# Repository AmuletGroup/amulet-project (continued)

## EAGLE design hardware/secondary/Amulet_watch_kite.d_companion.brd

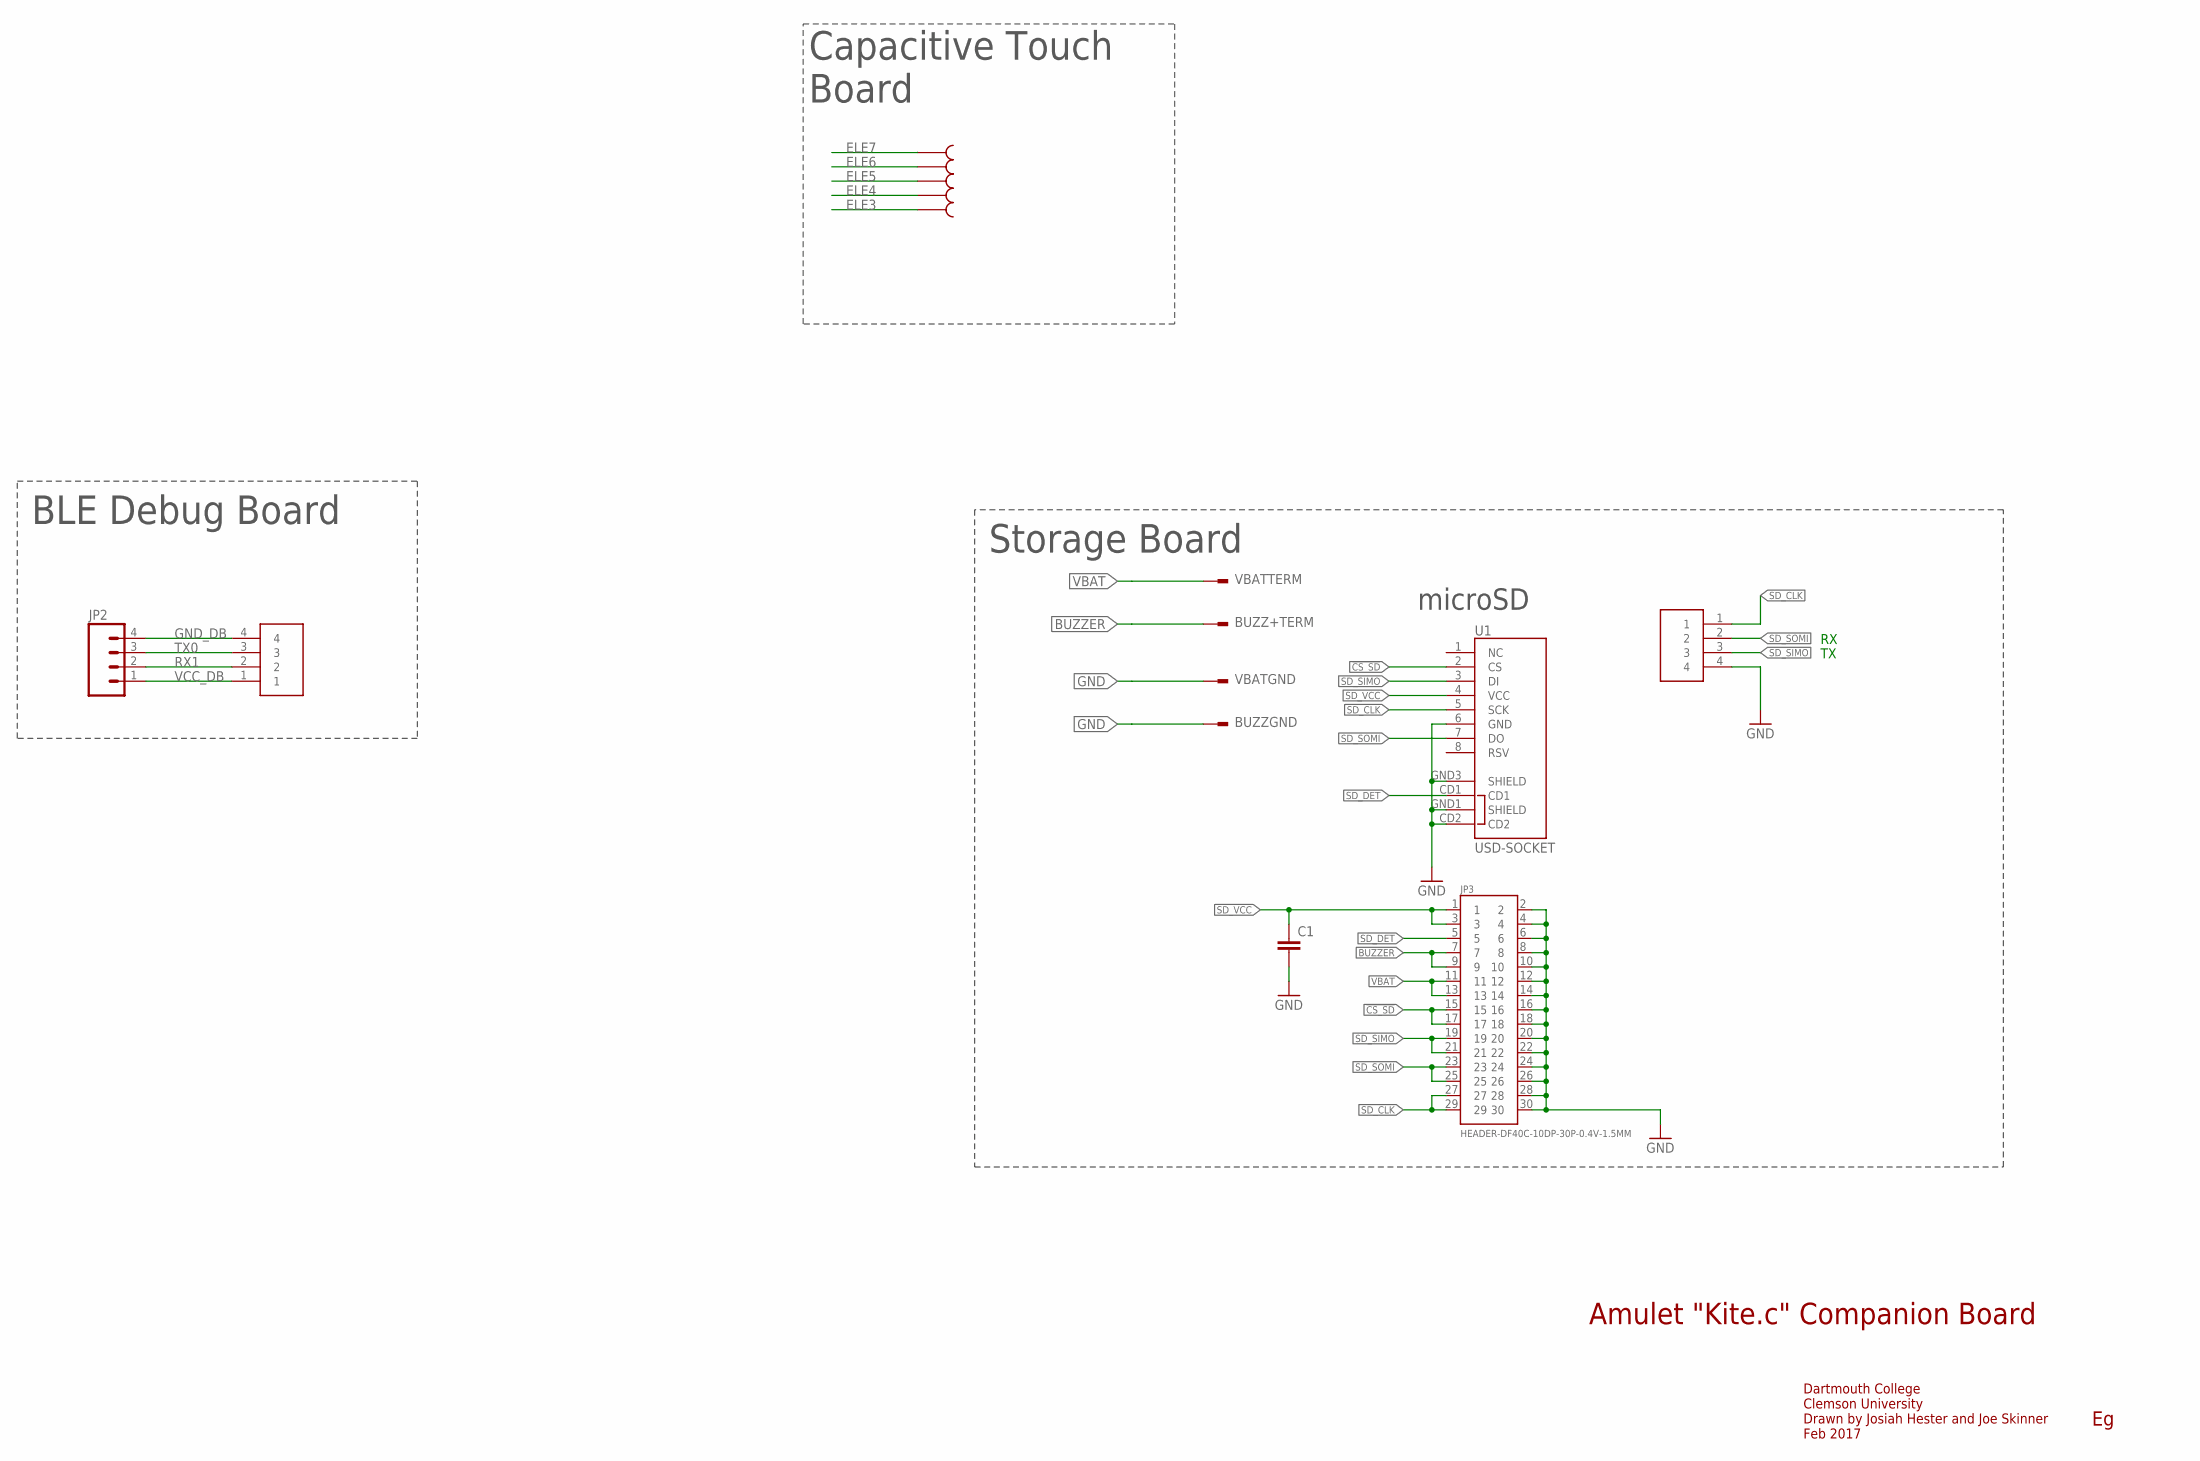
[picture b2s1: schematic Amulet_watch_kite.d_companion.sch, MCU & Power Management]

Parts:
BUZZ+TERM: KITE.C.TERMINAL; BATTERY_TERMINAL
BUZZGND: KITE.C.TERMINAL; BATTERY_TERMINAL
C1: CAP0805; 0805
JP2: M04LOCK; 1X04_LOCK
JP3: HEADER-DF40C-10DP-30P-0.4V-1.5MM; HEADER-DF40-30; DIGIKEY H11622CT-ND
U1: USD-SOCKET; MICROSD_1:1
U$1, U$2, U$3, U$4, U$5: CTPAD
U$11, U$12: 1.27MM-MILLMAX; 1X03-1.27MM
VBATGND: KITE.C.TERMINAL; BATTERY_TERMINAL
VBATTERM: KITE.C.TERMINAL; BATTERY_TERMINAL

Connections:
!CS_SD: JP3.15, JP3.17, U1.2 (CS)
BUZZER: BUZZ+TERM.P1, JP3.7, JP3.9
ELE3: U$5.P$1
ELE4: U$4.P$1
ELE5: U$3.P$1
ELE6: U$2.P$1
ELE7: U$1.P$1
GND: BUZZGND.P1, C1.2, JP3.2, JP3.4, JP3.6, JP3.8, JP3.10, JP3.12, JP3.14, JP3.16, JP3.18, JP3.20, JP3.22, JP3.24, JP3.26, JP3.28, JP3.30, U1.6 (GND), U1.CD2, U1.GND1 (SHIELD), U1.GND3 (SHIELD), U$11.4, VBATGND.P1
GND_DB: JP2.4, U$12.4
RX1: JP2.2, U$12.2
SD_CLK: JP3.27, JP3.29, U1.5 (SCK), U$11.1
SD_DET: JP3.5, U1.CD1
SD_SIMO: JP3.19, JP3.21, U1.3 (DI), U$11.3
SD_SOMI: JP3.23, JP3.25, U1.7 (DO), U$11.2
SD_VCC: C1.1, JP3.1, JP3.3, U1.4 (VCC)
TX0: JP2.3, U$12.3
VBAT: JP3.11, JP3.13, VBATTERM.P1
VCC_DB: JP2.1, U$12.1

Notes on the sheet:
Amulet "Kite.c" Companion Board
Dartmouth College Clemson University Drawn by Josiah Hester and Joe Skinner Feb 2017
microSD
Capacitive Touch Board
Storage Board
BLE Debug Board

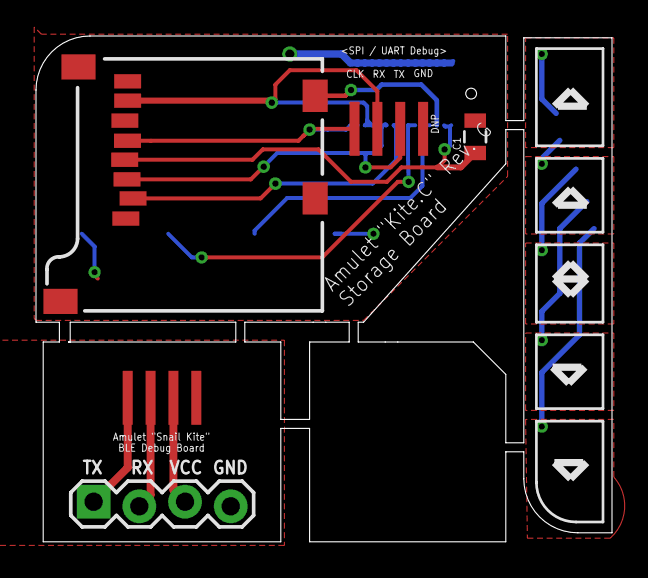
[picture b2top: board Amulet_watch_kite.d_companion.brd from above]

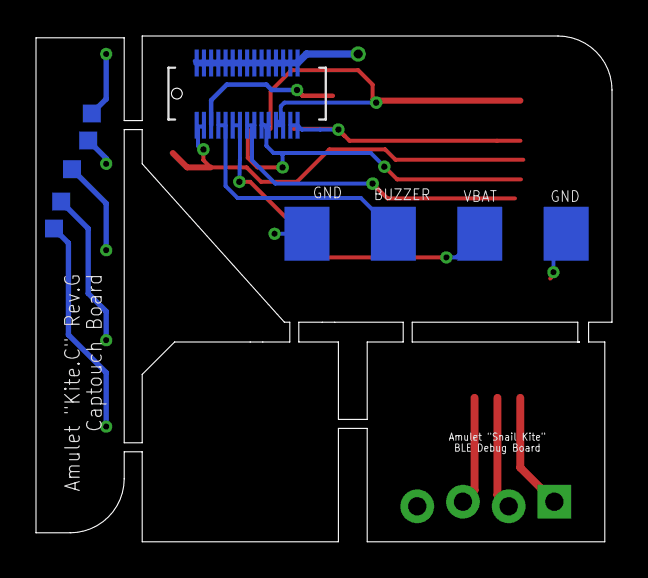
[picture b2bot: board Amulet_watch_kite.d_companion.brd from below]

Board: 2 copper layers, 32.0 x 28.1 mm, 15 parts (10 on the bottom side), 13 nets.

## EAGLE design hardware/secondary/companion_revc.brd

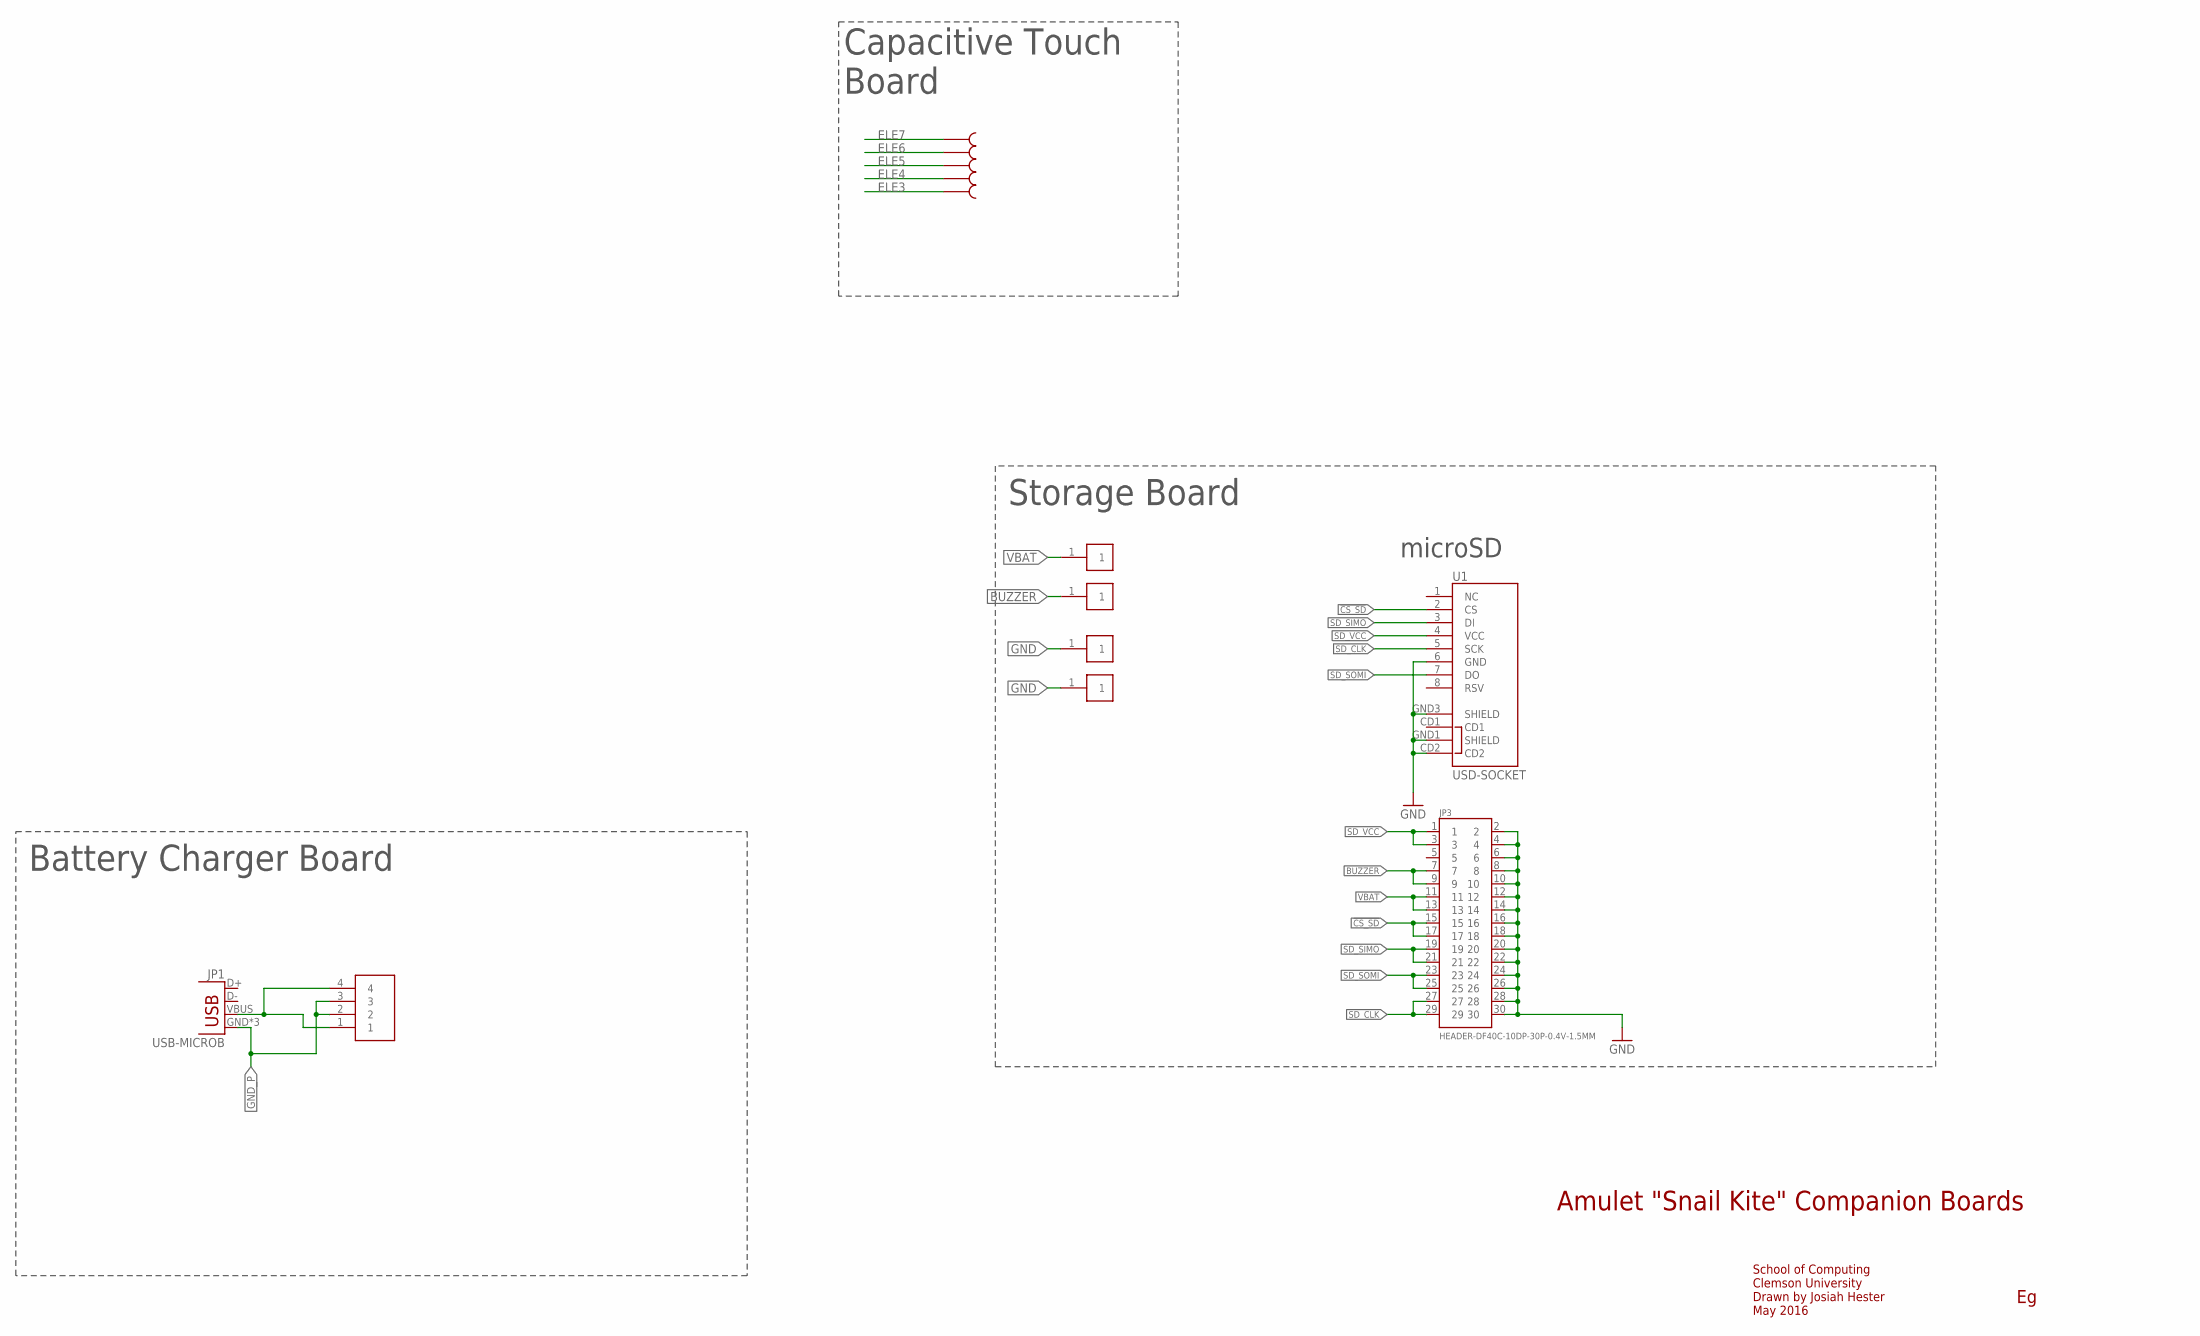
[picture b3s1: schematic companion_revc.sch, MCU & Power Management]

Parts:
JP1: USB-MICROB
JP3: HEADER-DF40C-10DP-30P-0.4V-1.5MM; HEADER-DF40-30
U1: USD-SOCKET; MICROSD_1:1
U$1, U$2, U$3, U$4, U$5: CTPAD
U$6, U$7, U$8, U$9: 1PAD; 5X23MM_PAD
U$10: 1.27MM-MILLMAX; 1X03-1.27MM

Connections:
!CS_SD: JP3.15, JP3.17, U1.2 (CS)
BUZZER: JP3.7, JP3.9, U$7.1
ELE3: U$5.P$1
ELE4: U$4.P$1
ELE5: U$3.P$1
ELE6: U$2.P$1
ELE7: U$1.P$1
GND: JP3.2, JP3.4, JP3.6, JP3.8, JP3.10, JP3.12, JP3.14, JP3.16, JP3.18, JP3.20, JP3.22, JP3.24, JP3.26, JP3.28, JP3.30, U1.6 (GND), U1.CD2, U1.GND1 (SHIELD), U1.GND3 (SHIELD), U$8.1, U$9.1
GND_P: JP1.GND, JP1.MT1 (GND), JP1.MT2 (GND), U$10.2, U$10.3
SD_CLK: JP3.27, JP3.29, U1.5 (SCK)
SD_SIMO: JP3.19, JP3.21, U1.3 (DI)
SD_SOMI: JP3.23, JP3.25, U1.7 (DO)
SD_VCC: JP3.1, JP3.3, U1.4 (VCC)
USB_VIN: JP1.VBUS, U$10.1, U$10.4
VBAT: JP3.11, JP3.13, U$6.1

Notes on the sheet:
Amulet "Snail Kite" Companion Boards
School of Computing Clemson University Drawn by Josiah Hester May 2016
microSD
Capacitive Touch Board
Battery Charger Board
Storage Board

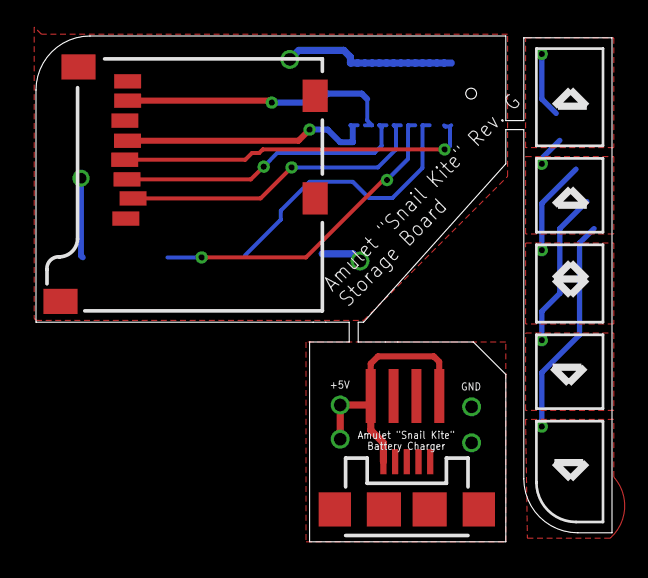
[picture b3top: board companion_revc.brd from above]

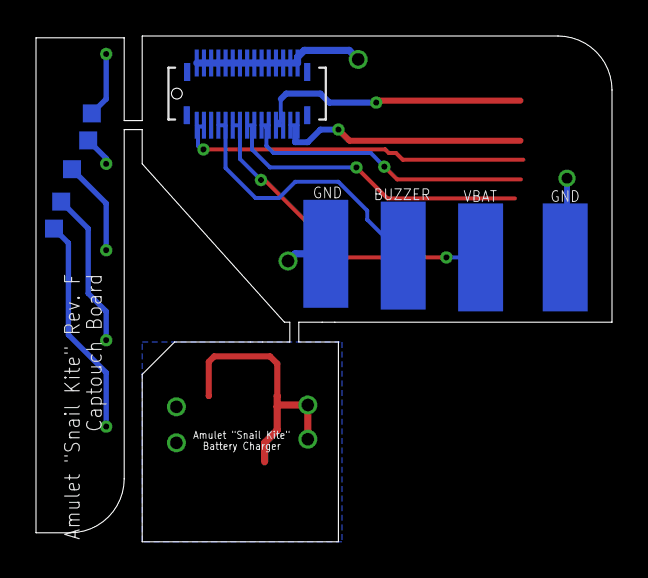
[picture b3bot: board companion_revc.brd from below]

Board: 2 copper layers, 32.0 x 28.1 mm, 13 parts (10 on the bottom side), 10 nets.

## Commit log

2016-08-31 Removed TODO
2016-08-31 Added license text to remaining files, and to CAD EAGLE schematics.
2016-09-08 updated modules
2016-09-08 corrected lib-qpc path
2016-09-21 updated paths for cloning git repo
2016-09-25 Moving lib-qpc back into the native folder
2016-09-26 Misspelled configuration
2016-09-26 Try catch on parsing to skip errors.
2016-10-25 New hardware revision, better connector.
2016-10-25 Update to clock app.
2016-11-07 New case designs.
2016-11-15 updating blink application
2016-11-15 adding readme files for applications
2016-11-15 updating pedometer and uidemo apps
2016-11-15 updated pedometer and uidemo apps
2016-11-15 updated readme files for pedometer and uidemo
2016-11-15 added readme files for ema and heartrate
2016-11-15 updated firmware and software readme files
2016-11-15 updated broken link in software readme
2016-11-15 updated getting started guide
2016-11-15 added image of example qm application
2016-11-15 updated links in example firmware config file and broken link in software readme
2016-11-15 updated ARP view link
2016-11-15 Added submodule commands in case recursive flag does not work
2016-11-15 updated sd card code for the amulet kite hardware version
2016-11-15 added bug tracking note to readme
2016-11-15 removed bugs file
2016-11-15 created issues subsection
2017-05-23 updated the getting started guide. Added picture for programmer hookup
2017-05-23 added programmer hookup picture
2017-05-23 updated picture link
2017-06-01 added image of new hardware rev
2017-06-01 updated image links to point to new hardware
2017-06-01 removed HTML style attribute because it is not supported by github
2017-06-01 moving image position
2017-06-01 moved image to hardware
2017-06-01 floating right appears to work better with git than floating left
2017-06-01 removed old hardware pictures
2017-06-01 adding assembly guides for updated hardware
2017-06-01 updated links for new assembly guides
2017-06-01 removing kiteb case files
2017-06-01 added case files for kitec
2017-06-01 typo fix
2017-06-01 removing kiteb eagle files
2017-06-01 adding eagle files for kitec
2017-06-01 removed kiteb assembly guide
2017-06-01 removed cam files for kiteb
2017-06-01 added gerbers for kitec
2018-04-02 renamed native folder to match internal repo
2018-04-02 commit of firmware for next open release
2018-04-02 commit of ble for next open release
2018-04-02 updated software folder name to match internal repo
2018-04-02 removed old setup files
2018-04-02 added new environment setup scripts
2018-04-02 updated getting started guide to use new setup scripts
2018-04-02 added pictures used in updated getting started guide
2018-04-03 updated linux buildscript and fixed clone link in GETTING_STARTED
2018-04-04 updated app dev guide as well as config file paths
2018-04-26 Actually fits a 20mm watch band
2018-06-28 updated contributors list
2018-09-20 updated high level readme files
2018-09-20 adding template app that is used in getting started guide
2018-09-20 removed outdated code and files related to old hardware versions
2018-09-20 added a TOC and fixed some formatting errors
2018-09-20 added setup for windows
2018-09-20 fixed typo
2018-10-04 fixed FIFO read bug
2018-10-04 Added instructions for downloading and setting up our Linux VM
2018-10-04 fixed a typo in one of the default gcc root paths
2018-10-04 changed the syntax of attribute section on several global variables as gcc v7 does not like it and throws an error
2018-10-04 updated msp430-elf-size path
2018-10-04 updated path for libqp
2018-10-04 removing libqp as it should be a submodule
2018-10-04 removing libqp submodule and adding precompiled library
2018-10-04 added libqp library
2018-10-04 removed space at beginning of gcc_root path which caused yaml parsing error
2018-10-04 removed whiteowl support
2018-10-04 adding libqp library
2018-10-18 removed old kitec hardware files
2018-10-18 added harware files for kited
2018-10-18 updated gyro library to support kited
2018-11-15 updated gyro model
